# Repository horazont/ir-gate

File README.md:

# Moved Repository

This repository moved to https://codeberg.org/jssfr/ir-gate.

This is in response to the many things wrong with GitHub, including but
not limited to what I see as blatant exploitation of people's work with
what Copilot is.

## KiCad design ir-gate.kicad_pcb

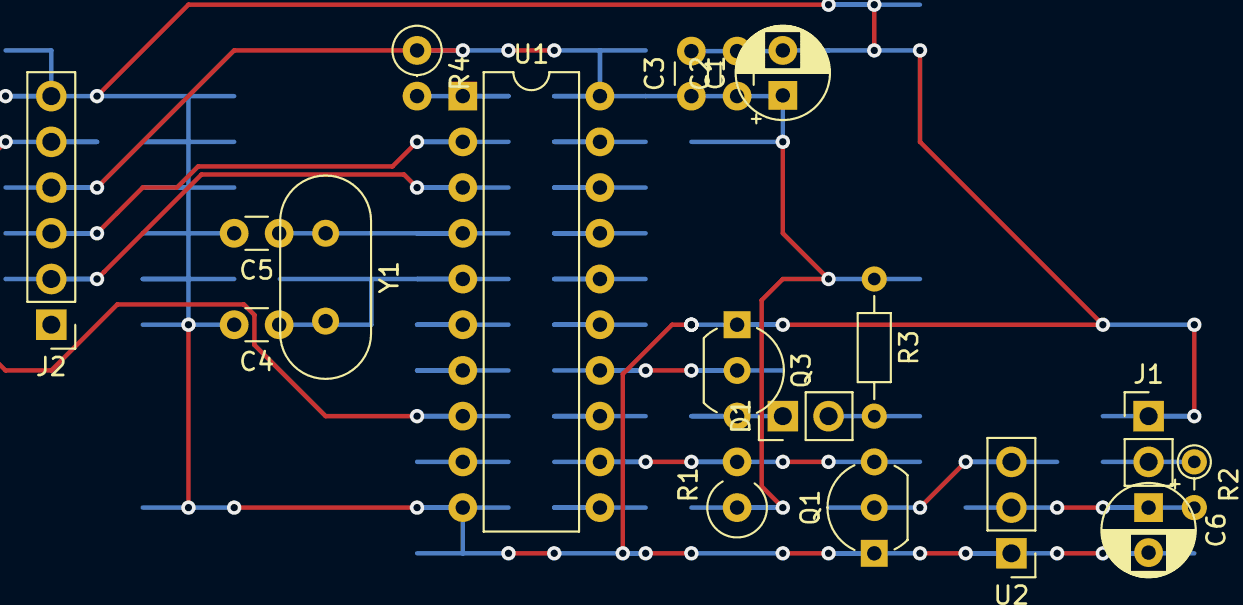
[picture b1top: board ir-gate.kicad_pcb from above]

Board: 2 copper layers, 18 parts (0 on the bottom side), 15 nets.

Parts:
C1: 1n; CP_Radial_D5.0mm_P2.50mm
C2: 100p; C_Disc_D3.0mm_W1.6mm_P2.50mm
C3: 10p; C_Disc_D3.0mm_W1.6mm_P2.50mm
C4, C5: C; C_Disc_D3.0mm_W1.6mm_P2.50mm
C6: 4.7u; CP_Radial_D5.0mm_P2.50mm
D1: LED; PinHeader_1x02_P2.54mm_Vertical
J1: Conn_01x02; PinHeader_1x02_P2.54mm_Vertical
J2: Conn_01x06; PinHeader_1x06_P2.54mm_Vertical
Q1, Q3: 2N7000; TO-92_Inline_Wide
R1: R; R_Axial_DIN0309_L9.0mm_D3.2mm_P2.54mm_Vertical
R2: 100; R_Axial_DIN0204_L3.6mm_D1.6mm_P2.54mm_Vertical
R3: R; R_Axial_DIN0204_L3.6mm_D1.6mm_P7.62mm_Horizontal
R4: R; R_Axial_DIN0207_L6.3mm_D2.5mm_P2.54mm_Vertical
U1: ATtiny2313A-PU; DIP-20_W7.62mm
U2: TSOP17xx; PinHeader_1x03_P2.54mm_Vertical
Y1: Crystal; Crystal_HC49-U_Vertical

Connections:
/CTS: J2.5, U1.8
/IR: Q1.2, U2.3
/MOD: Q3.2, U1.14
/RXD: J2.3, U1.2
/SIN1: Q1.3, R1.2, U1.12
/SOUT: D1.1, Q3.3
/TXD: J2.2, U1.3
/nRESET: R4.2, U1.1
GND: C1.2, C2.2, C3.2, C4.2, C5.2, C6.2, J1.1, J2.6, Q1.1, Q3.1, U1.10, U2.1
unnamed: C4.1, U1.5, Y1.2
unnamed: C5.1, U1.4, Y1.1
unnamed: C6.1, R2.2, U2.2
unnamed: D1.2, R3.2
VCC: C1.1, C2.1, C3.1, J2.4, R1.1, R3.1, R4.1, U1.20
VS: J1.2, R2.1

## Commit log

2022-01-29 Bootstrap src
2022-02-06 Bootstrap C code
    It generates 38 kHz!
2022-02-06 Implement IR repeater functionality
2022-02-06 Get rid of explicit state
    This reduces the program size and the delay when reacting to interrupts,
    as we do not have the expensive (in terms of computing) SRAM accesses
    anymore.
2022-02-06 Add support for sending the signal shape via uart
2022-02-06 Implement support for generating IR signals from USART commands
2022-02-06 Refine output controlling
2022-02-07 Rework sniffing mode to be more scalable
    Some IR signals require pulse lengths up to 9ms, some have pause lengths
    which are even longer.
    The previous UART protocol would simply emit an overflow for those and
    the entire thing would enter something resembling an undefined state. We
    don't want that.
    However, we have to stick to 8 bit messages, because even with the (now
2022-02-07 Shave 18 bytes off
    No need to do multiple reads against BUFFER here, given that we only
    call this from within interrupt handlers and our interrupts do not nest.
2022-02-18 Make state machine clearer
2022-02-18 Do not invert the IR input
    We need a level shifter for the IR demodulator, because it runs on 5V,
    while the ATtiny2313a will run on 3.3V (to easier interface with the
    Pi).
    A simple N-FET based level shifter will cause the signal to be inverted.
    The TSOP1738 is active-low. That means that the input signal we receive
    will be the uninverted, demodulated IR signal (active-low + inversion =
2022-02-18 Make output inversion configurable
    This allows us to save one inversion stage on the output level shifter,
    too.
2022-02-26 Add schematics and "PCB" layout
2024-08-31 Boom
